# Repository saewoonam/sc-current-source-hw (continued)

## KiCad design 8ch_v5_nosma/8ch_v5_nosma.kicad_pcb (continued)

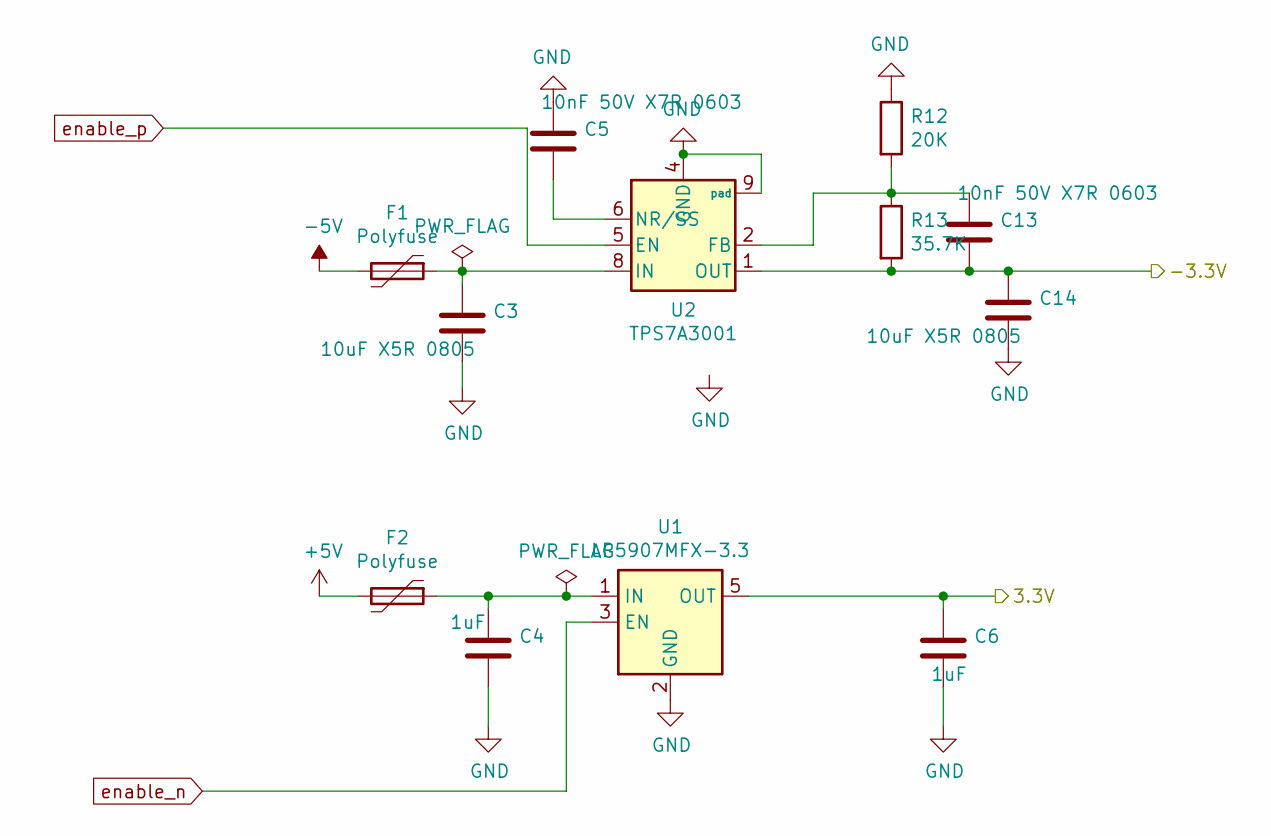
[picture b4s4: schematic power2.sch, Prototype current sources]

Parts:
C3, C14: 10uF X5R 0805; C_0805_2012Metric_Pad1.15x1.40mm_HandSolder; MPN CL21B106KPQNNNE
C4, C6: 1uF; C_0603_1608Metric_Pad1.05x0.95mm_HandSolder; MPN CL10B105KA8NNNC
C5, C13: 10nF 50V X7R 0603; C_0603_1608Metric_Pad1.05x0.95mm_HandSolder; MPN 0603B103K500NT
F1, F2: Polyfuse; Fuse_0603_1608Metric_Pad1.05x0.95mm_HandSolder; MPN TLC-FSMD020
R12: 20K; R_0603_1608Metric_Pad1.05x0.95mm_HandSolder; MPN 0603WAF2002T5E
R13: 35.7K; R_0603_1608Metric_Pad1.05x0.95mm_HandSolder; MPN 0603WAF3572T5E
U1: LP5907MFX-3.3; SOT-23-5; MPN LP5907MFX-3.3
U2: TPS7A3001; MSOP-8-1EP_3x3mm_P0.65mm_EP1.68x1.88mm; MPN TPS7A3001DGNR

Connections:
+5V: F2.2; also elsewhere on the board
-5V: F1.2; also elsewhere on the board
/Sheet5E20A415/sheet5E7AB32F/3.3V: C6.1, U1.5 (OUT); also elsewhere on the board
/Sheet5E20A415/sheet5E7AB32F/-3.3V: C13.2, C14.1, R13.2, U2.1 (OUT); also elsewhere on the board
GND: C3.2, C4.2, C5.1, C6.2, C14.2, R12.1, U1.2 (GND), U2.4 (GND), U2.9 (pad); also elsewhere on the board
unnamed: C3.1, F1.1, U2.8 (IN)
unnamed: C4.1, F2.1, U1.1 (IN)
unnamed: C5.2, U2.6 (NR/SS)
unnamed: C13.1, R12.2, R13.1, U2.2 (FB)
enable_n: U1.3 (EN); also elsewhere on the board
enable_p: U2.5 (EN); also elsewhere on the board

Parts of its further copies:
C46, C51, C52, C57, C58, C63, C64, C69, C70, C75, C76, C81, C82, C87: 10uF X5R 0805; C_0805_2012Metric_Pad1.15x1.40mm_HandSolder; MPN CL21B106KPQNNNE
C47, C49, C53, C55, C59, C61, C65, C67, C71, C73, C77, C79, C83, C85: 1uF; C_0603_1608Metric_Pad1.05x0.95mm_HandSolder; MPN CL10B105KA8NNNC
C48, C50, C54, C56, C60, C62, C66, C68, C72, C74, C78, C80, C84, C86: 10nF 50V X7R 0603; C_0603_1608Metric_Pad1.05x0.95mm_HandSolder; MPN 0603B103K500NT
F3, F4, F5, F6, F7, F8, F9, F10, F11, F12, F13, F14, F15, F16: Polyfuse; Fuse_0603_1608Metric_Pad1.05x0.95mm_HandSolder; MPN TLC-FSMD020
R33, R35, R37, R39, R41, R43, R45: 20K; R_0603_1608Metric_Pad1.05x0.95mm_HandSolder; MPN 0603WAF2002T5E
R34, R36, R38, R40, R42, R44, R46: 35.7K; R_0603_1608Metric_Pad1.05x0.95mm_HandSolder; MPN 0603WAF3572T5E
U3, U5, U7, U9, U11, U13, U15: LP5907MFX-3.3; SOT-23-5; MPN LP5907MFX-3.3
U4, U6, U8, U10, U12, U14, U16: TPS7A3001; MSOP-8-1EP_3x3mm_P0.65mm_EP1.68x1.88mm; MPN TPS7A3001DGNR

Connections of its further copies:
+5V: F4.2, F6.2, F8.2, F10.2, F12.2, F14.2, F16.2; also elsewhere on the board
-5V: F3.2, F5.2, F7.2, F9.2, F11.2, F13.2, F15.2; also elsewhere on the board
/sheet5E6FDFF3/sheet5E7AB32F/3.3V: C49.1, U3.5 (OUT); also elsewhere on the board
/sheet5E6FDFF3/sheet5E7AB32F/-3.3V: C50.2, C51.1, R34.2, U4.1 (OUT); also elsewhere on the board
/sheet5E70F675/sheet5E7AB32F/3.3V: C67.1, U9.5 (OUT); also elsewhere on the board
/sheet5E70F675/sheet5E7AB32F/-3.3V: C68.2, C69.1, R40.2, U10.1 (OUT); also elsewhere on the board
/sheet5E70F676/sheet5E7AB32F/3.3V: C73.1, U11.5 (OUT); also elsewhere on the board
/sheet5E70F676/sheet5E7AB32F/-3.3V: C74.2, C75.1, R42.2, U12.1 (OUT); also elsewhere on the board
/sheet5E70F677/sheet5E7AB32F/3.3V: C79.1, U13.5 (OUT); also elsewhere on the board
/sheet5E70F677/sheet5E7AB32F/-3.3V: C80.2, C81.1, R44.2, U14.1 (OUT); also elsewhere on the board
/sheet5E70F678/sheet5E7AB32F/3.3V: C85.1, U15.5 (OUT); also elsewhere on the board
/sheet5E70F678/sheet5E7AB32F/-3.3V: C86.2, C87.1, R46.2, U16.1 (OUT); also elsewhere on the board
/sheet5E7078C0/sheet5E7AB32F/3.3V: C55.1, U5.5 (OUT); also elsewhere on the board
/sheet5E7078C0/sheet5E7AB32F/-3.3V: C56.2, C57.1, R36.2, U6.1 (OUT); also elsewhere on the board
/sheet5E7078C1/sheet5E7AB32F/3.3V: C61.1, U7.5 (OUT); also elsewhere on the board
/sheet5E7078C1/sheet5E7AB32F/-3.3V: C62.2, C63.1, R38.2, U8.1 (OUT); also elsewhere on the board
GND: C46.2, C47.2, C48.1, C49.2, C51.2, C52.2, C53.2, C54.1, C55.2, C57.2, C58.2, C59.2, C60.1, C61.2, C63.2, C64.2, C65.2, C66.1, C67.2, C69.2, C70.2, C71.2, C72.1, C73.2, C75.2, C76.2, C77.2, C78.1, C79.2, C81.2, C82.2, C83.2, C84.1, C85.2, C87.2, R33.1, R35.1, R37.1, R39.1, R41.1, R43.1, R45.1, U3.2 (GND), U4.4 (GND), U4.9 (pad), U5.2 (GND), U6.4 (GND), U6.9 (pad), U7.2 (GND), U8.4 (GND), U8.9 (pad), U9.2 (GND), U10.4 (GND), U10.9 (pad), U11.2 (GND), U12.4 (GND), U12.9 (pad), U13.2 (GND), U14.4 (GND), U14.9 (pad), U15.2 (GND), U16.4 (GND), U16.9 (pad); also elsewhere on the board
unnamed: C46.1, F3.1, U4.8 (IN)
unnamed: C47.1, F4.1, U3.1 (IN)
unnamed: C48.2, U4.6 (NR/SS)
unnamed: C50.1, R33.2, R34.1, U4.2 (FB)
unnamed: C52.1, F5.1, U6.8 (IN)
unnamed: C53.1, F6.1, U5.1 (IN)
unnamed: C54.2, U6.6 (NR/SS)
unnamed: C56.1, R35.2, R36.1, U6.2 (FB)
unnamed: C58.1, F7.1, U8.8 (IN)
unnamed: C59.1, F8.1, U7.1 (IN)
unnamed: C60.2, U8.6 (NR/SS)
unnamed: C62.1, R37.2, R38.1, U8.2 (FB)
unnamed: C64.1, F9.1, U10.8 (IN)
unnamed: C65.1, F10.1, U9.1 (IN)
unnamed: C66.2, U10.6 (NR/SS)
unnamed: C68.1, R39.2, R40.1, U10.2 (FB)
unnamed: C70.1, F11.1, U12.8 (IN)
unnamed: C71.1, F12.1, U11.1 (IN)
unnamed: C72.2, U12.6 (NR/SS)
unnamed: C74.1, R41.2, R42.1, U12.2 (FB)
unnamed: C76.1, F13.1, U14.8 (IN)
unnamed: C77.1, F14.1, U13.1 (IN)
unnamed: C78.2, U14.6 (NR/SS)
unnamed: C80.1, R43.2, R44.1, U14.2 (FB)
unnamed: C82.1, F15.1, U16.8 (IN)
unnamed: C83.1, F16.1, U15.1 (IN)
unnamed: C84.2, U16.6 (NR/SS)
unnamed: C86.1, R45.2, R46.1, U16.2 (FB)
enable_n: U3.3 (EN), U5.3 (EN), U7.3 (EN), U9.3 (EN), U11.3 (EN), U13.3 (EN), U15.3 (EN); also elsewhere on the board
enable_p: U4.5 (EN), U6.5 (EN), U8.5 (EN), U10.5 (EN), U12.5 (EN), U14.5 (EN), U16.5 (EN); also elsewhere on the board

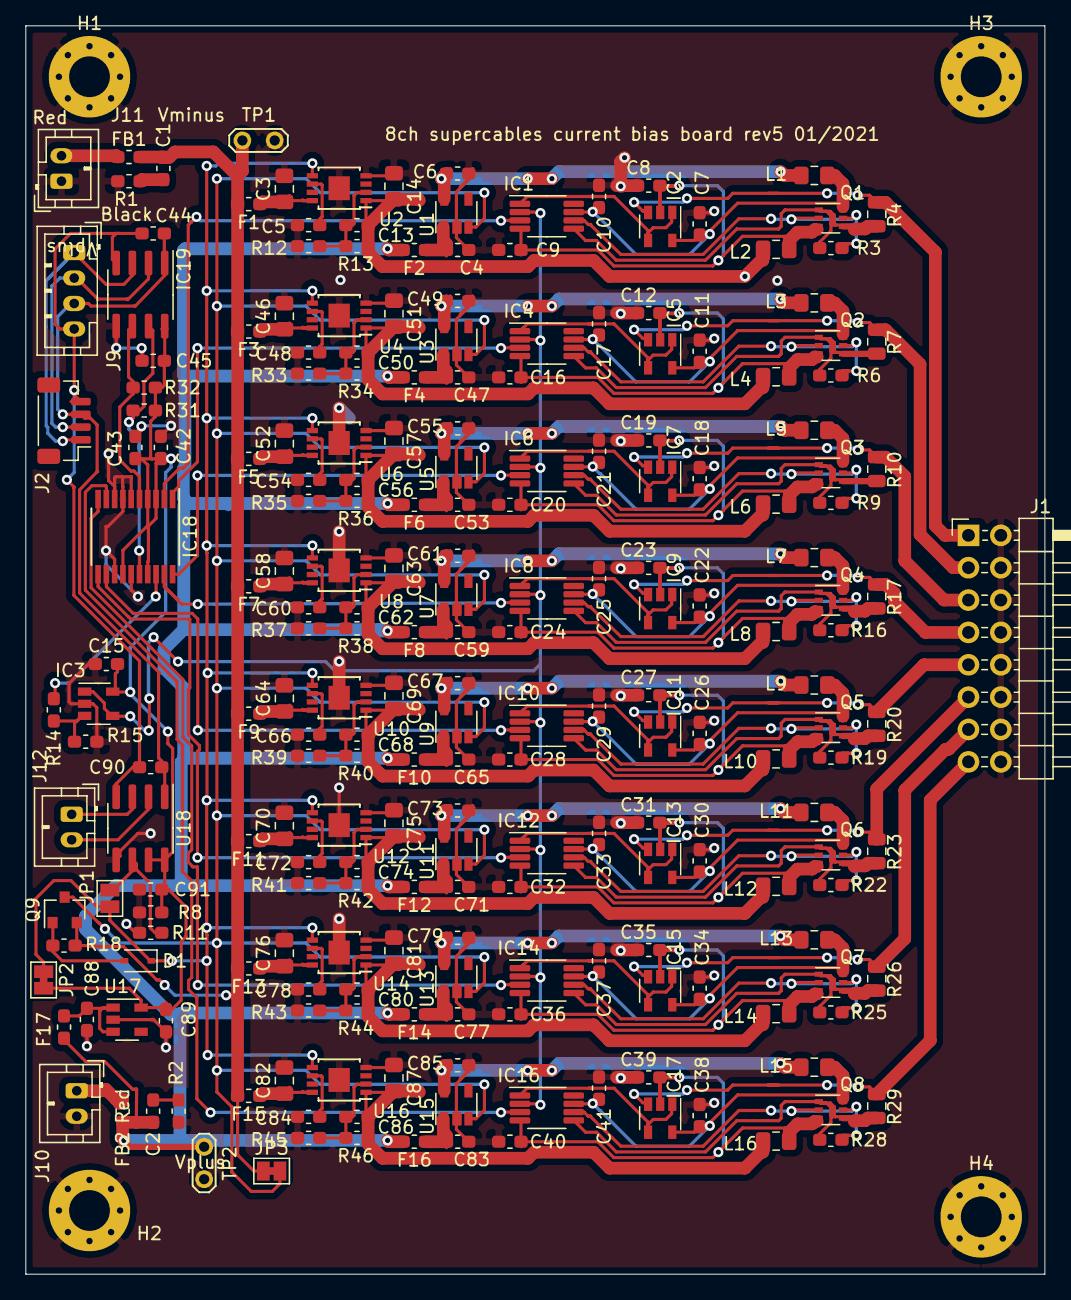
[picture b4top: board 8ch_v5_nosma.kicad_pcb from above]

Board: 2 copper layers, 80.0 x 98.0 mm, 229 parts (0 on the bottom side), 128 nets.

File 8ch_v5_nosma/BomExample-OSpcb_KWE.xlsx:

Designator | MPN | Qty | Description
C1, C2, C4, C6, C47, C49, C53, C55, C59, C61, C65, C67, C71, C73, C77, C79, C83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 | CL10B105KA8NNNC | 20 | 1uF
C3, C14, C46, C51, C52, C57, C58, C63, C64, C69, C70, C75, C76, C81, C82, C87, | CL31B106KBHNNNE | 16 | 10uF X5R 0805
C5, C13, C48, C50, C54, C56, C60, C62, C66, C68, C72, C74, C78, C80, C84, C86, | 0603B103K500NT | 16 | 10nF 50V X7R 0603
C7, C8, C9, C10, C11, C12, C15, C16, C17, C18, C19, C20, C21, C22, C23, C24, C2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 | CC0603KPX7R7BB104 | 37 | 100nF
F1, F2, F3, F4, F5, F6, F7, F8, F9, F10, F11, F12, F13, F14, F15, F16, F17, | TLC-FSMD020 | 17 | Polyfuse
FB1, FB2, | BLM18PG181SN1D | 2 | BLM18PG181SN1D
H1, H2, H3, H4, | DNI | 4 | MountingHole_Pad
IC1, IC4, IC6, IC8, IC10, IC12, IC14, IC16, | AD8276ARMZ | 8 | AD8276
IC2, IC3, IC5, IC7, IC9, IC11, IC13, IC15, IC17, | OPA376AIDBVR | 9 | OPA376xxDBVR
IC18, | AD5675RBRUZ | 1 | AD5675RBRUZ
IC19, | ISO1541DR | 1 | ISO1541DR
J1, J2, J3, J4, J5, J6, J7, J8, | SMA-KWE20 | 8 | Conn_Coaxial
J9, | B4B-PH-K-S(LF)(SN) | 1 | B4B-PH-K
J10, J11, | B2B-PH-K-S(LF)(SN) | 2 | JST B2B-PH-K
JP1, JP2, JP3, JP4, JP5, JP6, JP7, JP8, | DNI | 8 | SolderJumper_3_Open
L1, L2, L3, L4, L5, L6, L7, L8, L9, L10, L11, L12, L13, L14, L15, L16, | MMZ2012Y152BTD25 | 16 | MMZ2012Y152B
Q1, Q2, Q3, Q4, Q5, Q6, Q7, Q8, | MMDT3946-7-F | 8 | MMDT3946-7-F
R1, R2, | RC0603FR-072RL | 2 | 2
R3, R6, R9, R14, R15, R16, R19, R22, R25, R28, | RC0603FR-071KL | 10 | 1k
R4, R7, R10, R17, R20, R23, R26, R29, | 2-1625868-7 | 8 | 10 0.1%
R5, R8, R11, R18, R21, R24, R27, R30, | ERA-6AEB102V | 8 | 1k 0.1%
R12, R33, R35, R37, R39, R41, R43, R45, | 0603WAF2002T5E | 8 | 20K
R13, R34, R36, R38, R40, R42, R44, R46, | 0603WAF3572T5E | 8 | 35.7K
R31, R32, | 0603WAF1002T5E | 2 | 10K
U1, U3, U5, U7, U9, U11, U13, U15, U17, | LP5907MFX-3.3 | 9 | LP5907MFX-3.3
U2, U4, U6, U8, U10, U12, U14, U16, | TPS7A3001DGNR | 8 | TPS7A3001

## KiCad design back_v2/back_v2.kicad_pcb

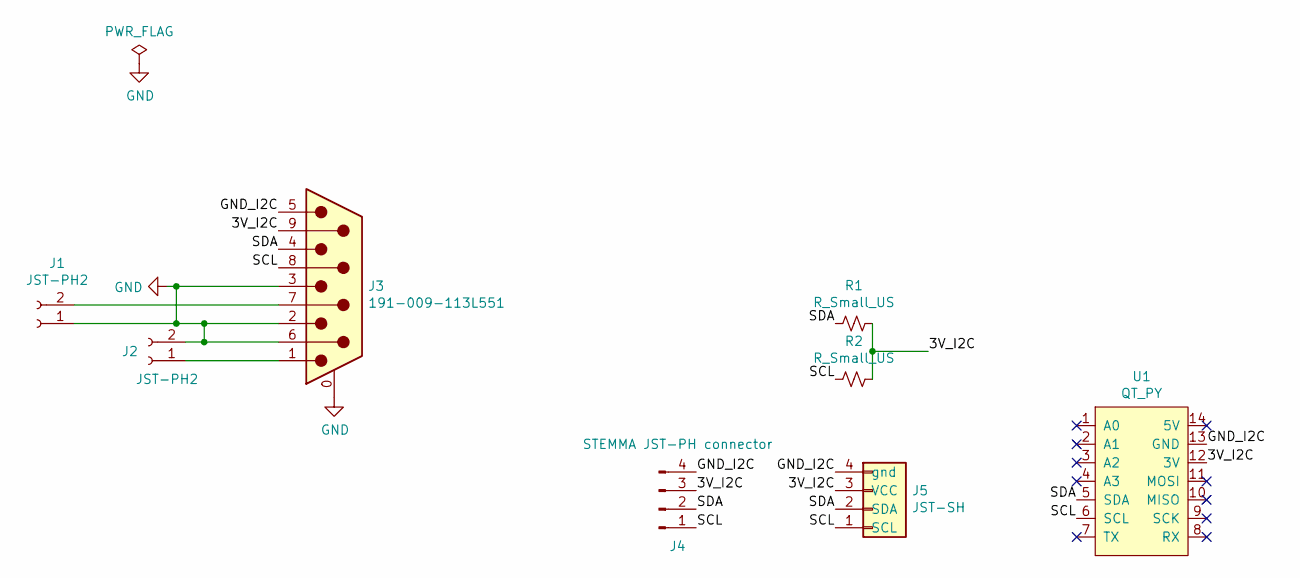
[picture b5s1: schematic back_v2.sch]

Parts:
J1, J2: JST-PH2; JST_PH_B2B-PH-SM4-TB_1x02-1MP_P2.00mm_Vertical; MPN B2B-PH-SM4-TB(lf)(sn)
J3: 191-009-113L551; DSUB-9_Male_Vertical_P2.77x2.84mm_MountingHoles; MPN 191-009-113L551
J4: STEMMA JST-PH connector; JST_PH_B4B-PH-SM4-TB_1x04-1MP_P2.00mm_Vertical; MPN B4B-PH-SM4-TB(lf)(sn)
J5: JST-SH; JST_SH_BM04B-SRSS-TB_1x04-1MP_P1.00mm_Vertical; MPN JST-SH-BM04B-SRSS-TB
R1, R2: R_Small_US; R_0603_1608Metric_Pad1.05x0.95mm_HandSolder
U1: QT_PY

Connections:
/3V_I2C: J3.9, J4.3, J5.3 (VCC), R1.1, R2.1, U1.12 (3V)
/GND_I2C: J3.5, J4.4, J5.4 (gnd), U1.13 (GND)
/SCL: J3.8, J4.1, J5.1 (SCL), R2.2, U1.6 (SCL)
/SDA: J3.4, J4.2, J5.2 (SDA), R1.2, U1.5 (SDA)
GND: J1.1, J2.2, J3.0 (PAD), J3.2, J3.3, J3.6
unnamed: J1.2, J3.7
unnamed: J2.1, J3.1

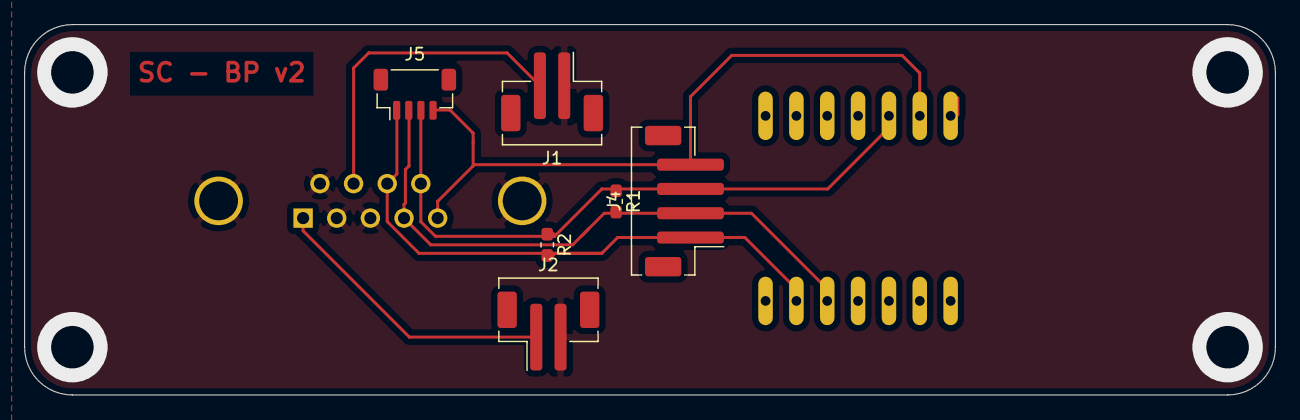
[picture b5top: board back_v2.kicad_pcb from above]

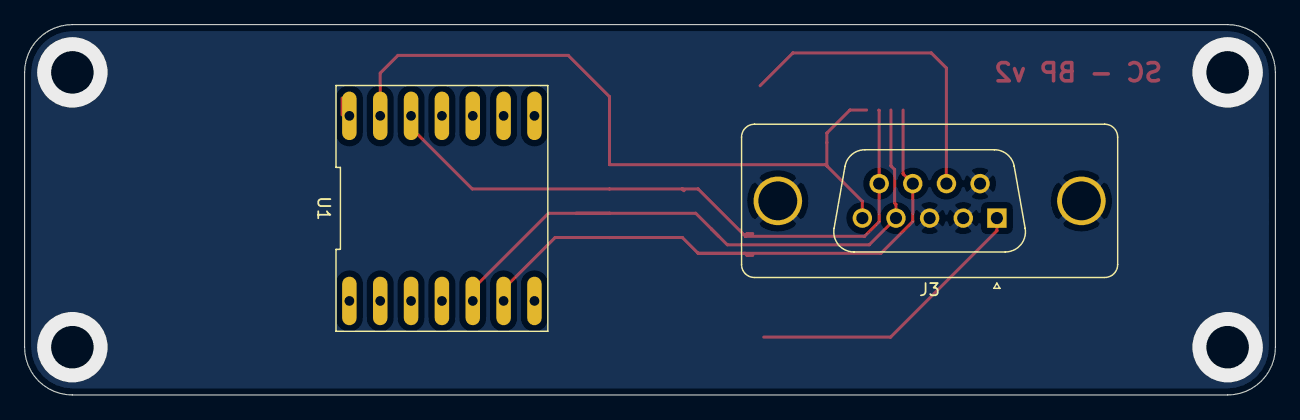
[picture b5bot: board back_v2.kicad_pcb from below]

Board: 2 copper layers, 103.0 x 30.5 mm, 8 parts (2 on the bottom side), 7 nets.

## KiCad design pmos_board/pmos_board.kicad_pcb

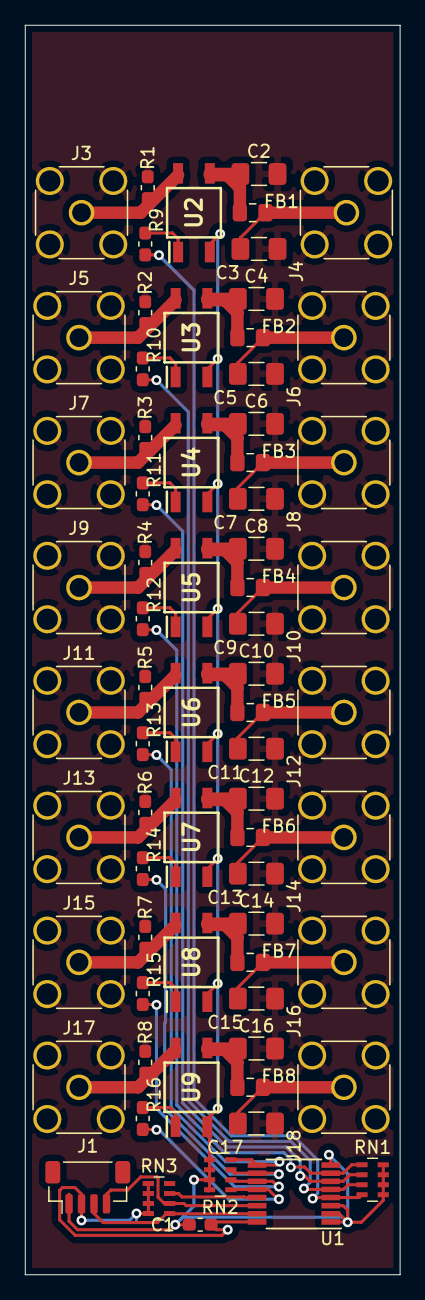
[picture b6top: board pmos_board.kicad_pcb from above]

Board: 2 copper layers, 30.0 x 100.0 mm, 70 parts (0 on the bottom side), 46 nets.

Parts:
C1: 100nF; C_0603_1608Metric_Pad1.05x0.95mm_HandSolder
C2, C3, C4, C5, C6, C7, C8, C9, C10, C11, C12, C13, C14, C15, C16, C17: 100uF; C_1206_3216Metric_Pad1.42x1.75mm_HandSolder
FB1, FB2, FB3, FB4, FB5, FB6, FB7, FB8: Ferrite_Bead; L_0805_2012Metric_Pad1.15x1.40mm_HandSolder
J1: Conn_01x04; JST_SH_BM04B-SRSS-TB_1x04-1MP_P1.00mm_Vertical
J3, J4, J5, J6, J7, J8, J9, J10, J11, J12, J13, J14, J15, J16, J17, J18: Conn_Coaxial; SMA_Amphenol_132134_Vertical
R1, R2, R3, R4, R5, R6, R7, R8: 10K 0.1%; R_0603_1608Metric_Pad1.05x0.95mm_HandSolder
R9, R10, R11, R12, R13, R14, R15, R16: 390; R_0603_1608Metric_Pad1.05x0.95mm_HandSolder
RN1, RN2, RN3: 4 x 10K ohm; R_Array_Concave_4x0603
U1: TCA9534APWR; TSSOP-16_4.4x5mm_P0.65mm
U2, U3, U4, U5, U6, U7, U8, U9: AQY212GSZ; AQY211G2S_samacsys

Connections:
+3V3: C1.2, J1.2, RN3.1, RN3.2, RN3.3, RN3.4, U1.16
/scl: J1.4, RN3.6, U1.14
/sda: J1.3, RN3.5, U1.15
/sw1: R9.2, RN1.4, U1.4
/sw2: R10.2, RN1.3, U1.5
/sw3: R11.2, RN1.2, U1.6
/sw4: R12.2, RN1.1, U1.7
/sw5: R13.2, RN2.4, U1.9
/sw6: R14.2, RN2.3, U1.10
/sw7: R15.2, RN2.2, U1.11
/sw8: R16.2, RN2.1, U1.12
GND: C2.2, C3.2, C4.2, C5.2, C6.2, C7.2, C8.2, C9.2, C10.2, C11.2, C12.2, C13.2, C14.2, C15.2, C16.2, C17.2, J3.2, J4.2, J5.2, J6.2, J7.2, J8.2, J9.2, J10.2, J11.2, J12.2, J13.2, J14.2, J15.2, J16.2, J17.2, J18.2, R1.2, R2.2, R3.2, R4.2, R5.2, R6.2, R7.2, R8.2
GNDD: C1.1, J1.1, RN1.5, RN1.6, RN1.7, RN1.8, RN2.5, RN2.6, RN2.7, RN2.8, U1.1, U1.2, U1.3, U1.8, U2.2, U3.2, U4.2, U5.2, U6.2, U7.2, U8.2, U9.2
unnamed: C2.1, FB1.2, U2.3
unnamed: C3.1, FB1.1, J4.1
unnamed: C4.1, FB2.2, U3.3
unnamed: C5.1, FB2.1, J6.1
unnamed: C6.1, FB3.2, U4.3
unnamed: C7.1, FB3.1, J8.1
unnamed: C8.1, FB4.2, U5.3
unnamed: C9.1, FB4.1, J10.1
unnamed: C10.1, FB5.2, U6.3
unnamed: C11.1, FB5.1, J12.1
unnamed: C12.1, FB6.2, U7.3
unnamed: C13.1, FB6.1, J14.1
unnamed: C14.1, FB7.2, U8.3
unnamed: C15.1, FB7.1, J16.1
unnamed: C16.1, FB8.2, U9.3
unnamed: C17.1, FB8.1, J18.1
unnamed: J3.1, R1.1, U2.4
unnamed: J5.1, R2.1, U3.4
unnamed: J7.1, R3.1, U4.4
unnamed: J9.1, R4.1, U5.4
unnamed: J11.1, R5.1, U6.4
unnamed: J13.1, R6.1, U7.4
unnamed: J15.1, R7.1, U8.4
unnamed: J17.1, R8.1, U9.4
unnamed: R9.1, U2.1
unnamed: R10.1, U3.1
unnamed: R11.1, U4.1
unnamed: R12.1, U5.1
unnamed: R13.1, U6.1
unnamed: R14.1, U7.1
unnamed: R15.1, U8.1
unnamed: R16.1, U9.1
unnamed: RN3.7, U1.13

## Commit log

2020-12-09 Add all hardware cad files
2020-12-09 Add assembly instructions
2020-12-09 Upddate assembly instructions
2020-12-09 tweak insructions
2021-01-21 t add pmos boaard
2021-01-24 Update to pmosboard
2021-01-24 add power (inside 8ch_v5_nosma) add back panel add front panel
2021-01-24 fix problem with front-panel... elminate thermals
2021-01-24 Add gerbers for front_v3
2021-02-05 update back_v3
2021-02-15 Add github actions
2021-02-15 try to cd to js directory in action
2021-02-15 concat cd and node
2021-02-15 update generated
2021-02-15 write index.html in index.js
2021-02-15 fix bug, branch_name
2021-02-15 Fix typo
2021-02-15 Deploying to gh-pages from @ saewoonam/sc-current-source-hw@bd3cb740d1f14cecc7fbb63238429e9ac98ea0c0 🚀
2021-02-15 Initial gh-pages commit
2021-02-15 Update link of redirect does not work
2021-02-15 Deploying to gh-pages from @ saewoonam/sc-current-source-hw@049e25174383fce190af3b879d9f692b3afc4d0b 🚀
2021-02-15 rearrange folders
2021-02-15 try to put all the web rendering stuff in 'web' folder
2021-02-15 Deploying to gh-pages from @ saewoonam/sc-current-source-hw@b3fa2927267bd49a98c33be9996e8accf7927c34 🚀
